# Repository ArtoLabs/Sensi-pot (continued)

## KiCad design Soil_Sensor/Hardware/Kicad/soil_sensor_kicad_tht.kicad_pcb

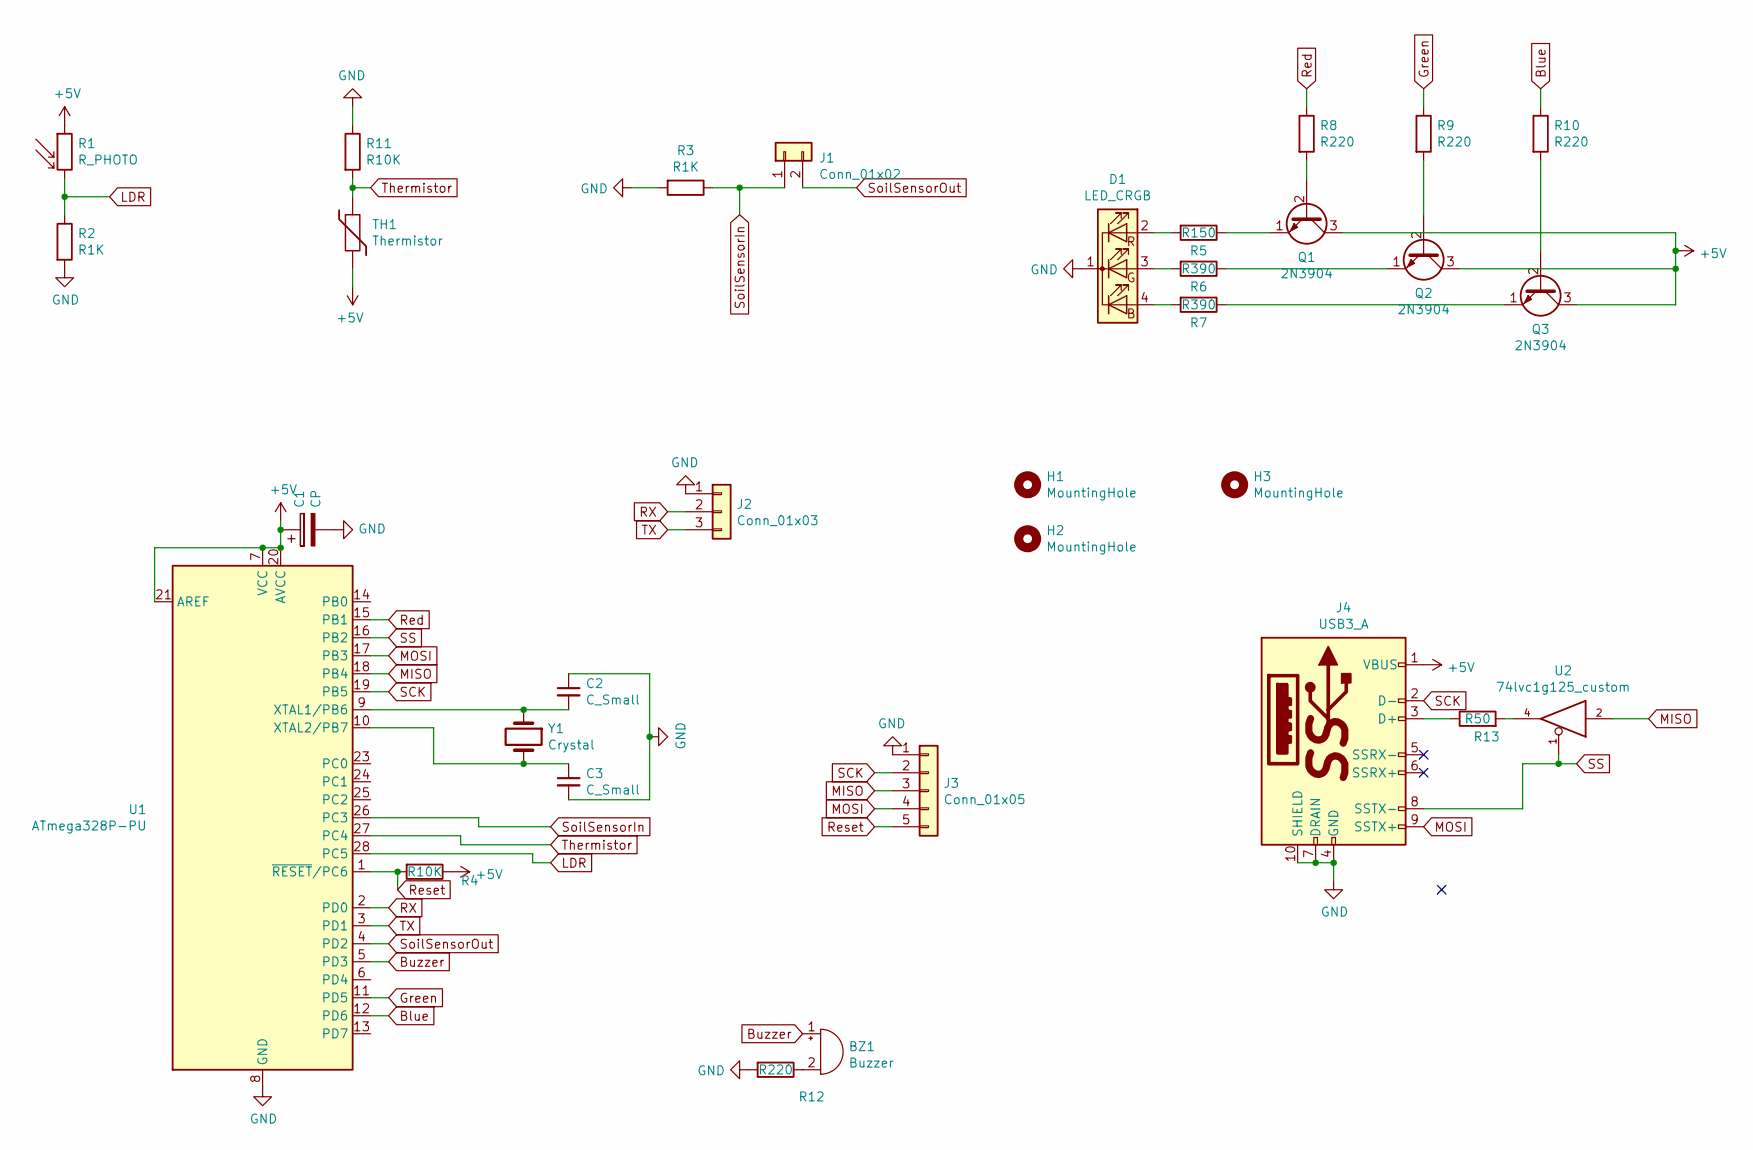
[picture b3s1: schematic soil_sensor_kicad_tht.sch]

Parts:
BZ1: Buzzer; Buzzer_12x9.5RM7.6
C1: CP; CP_Radial_D4.0mm_P1.50mm_bigger_pads
C2, C3: C_Small; C_Disc_D3.0mm_W1.6mm_P2.50mm
D1: LED_CRGB; LED_D5.0mm-4_RGB_Common_Cathode_2
H1, H2, H3: MountingHole; MountingHole_3.2mm_M3
J1: Conn_01x02; PinHeader_1x02_P2.54mm_Vertical
J2: Conn_01x03; PinHeader_1x03_P2.54mm_Vertical
J3: Conn_01x05; PinHeader_1x05_P2.54mm_Vertical
J4: USB3_A; USB3_A_Molex_Edited
Q1, Q2, Q3: 2N3904; TO-92_Inline_bigger_pads
R1: R_PHOTO; R_Axial_DIN0204_L3.6mm_D1.6mm_P1.90mm_Vertical
R2, R3: R1K; R_Axial_DIN0204_L3.6mm_D1.6mm_P7.62mm_Horizontal_bigger_pad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
R4, R11: R10K; R_Axial_DIN0204_L3.6mm_D1.6mm_P7.62mm_Horizontal_bigger_pad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
R5: R150; R_Axial_DIN0204_L3.6mm_D1.6mm_P7.62mm_Horizontal_bigger_pad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
R6, R7: R390; R_Axial_DIN0204_L3.6mm_D1.6mm_P7.62mm_Horizontal_bigger_pad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
R8, R9, R10, R12: R220; R_Axial_DIN0204_L3.6mm_D1.6mm_P7.62mm_Horizontal_bigger_pad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
R13: R50; R_Axial_DIN0204_L3.6mm_D1.6mm_P7.62mm_Horizontal_bigger_pad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
TH1: Thermistor; R_Axial_DIN0204_L3.6mm_D1.6mm_P1.90mm_Vertical
U1: ATmega328P-PU; DIP-28_W7.62mm
U2: 74lvc1g125_custom; SOT-23-5_HandSoldering
Y1: Crystal; Crystal_HC18-U_Vertical

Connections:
+5V: C1.1, J4.1 (VBUS), Q1.3 (C), Q2.3 (C), Q3.3 (C), R1.1, R4.1, TH1.2, U1.7 (VCC), U1.20 (AVCC), U1.21 (AREF), U2.5 (VCC)
Blue: R10.1, U1.12 (PD6)
Buzzer: BZ1.1 (-), U1.5 (PD3)
GND: C1.2, C2.1, C3.2, D1.1 (K), J2.1, J3.1, J4.4 (GND), J4.7 (DRAIN), J4.10 (SHIELD), R2.2, R3.2, R11.1, R12.2, U1.8 (GND), U1.22 (GND), U2.3 (GND)
Green: R9.1, U1.11 (PD5)
LDR: R1.2, R2.1, U1.28 (PC5)
MISO: J3.3, U1.18 (PB4), U2.2
MOSI: J3.4, J4.9 (SSTX+), U1.17 (PB3)
unnamed: BZ1.2 (+), R12.1
unnamed: C2.2, U1.9 (XTAL1/PB6), Y1.1
unnamed: C3.1, U1.10 (XTAL2/PB7), Y1.2
unnamed: D1.2 (RA), R5.2
unnamed: D1.3 (GA), R6.2
unnamed: D1.4 (BA), R7.2
unnamed: J4.3 (D+), R13.1
unnamed: Q1.1 (E), R5.1
unnamed: Q1.2 (B), R8.2
unnamed: Q2.1 (E), R6.1
unnamed: Q2.2 (B), R9.2
unnamed: Q3.1 (E), R7.1
unnamed: Q3.2 (B), R10.2
unnamed: R13.2, U2.4
RX: J2.2, U1.2 (PD0)
Red: R8.1, U1.15 (PB1)
Reset: J3.5, R4.2, U1.1 (~RESET~/PC6)
SCK: J3.2, J4.2 (D-), U1.19 (PB5)
SS: J4.8 (SSTX-), U1.16 (PB2), U2.1
SoilSensorIn: J1.1, R3.1, U1.26 (PC3)
SoilSensorOut: J1.2, U1.4 (PD2)
TX: J2.3, U1.3 (PD1)
Thermistor: R11.2, TH1.1, U1.27 (PC4)

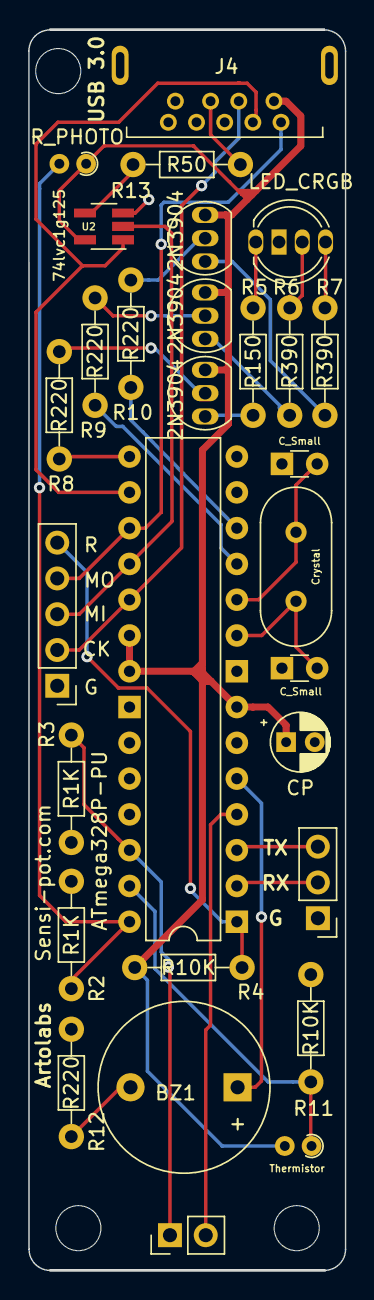
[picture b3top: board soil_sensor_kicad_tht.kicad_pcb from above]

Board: 2 copper layers, 22.5 x 88.1 mm, 32 parts (0 on the bottom side), 31 nets.

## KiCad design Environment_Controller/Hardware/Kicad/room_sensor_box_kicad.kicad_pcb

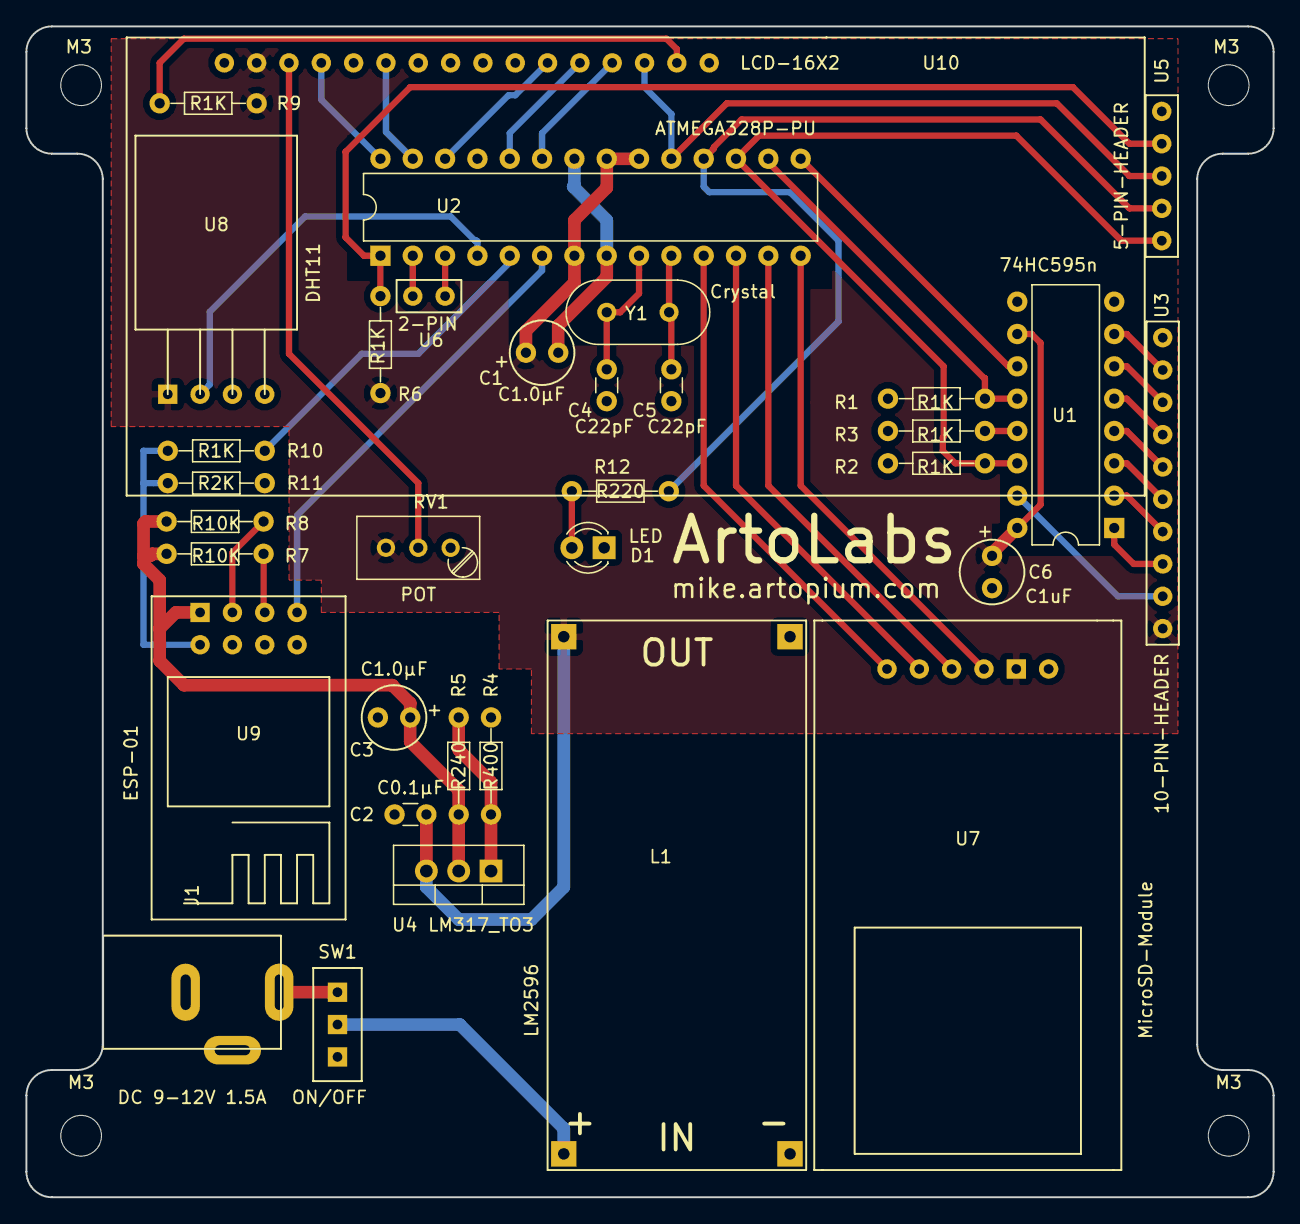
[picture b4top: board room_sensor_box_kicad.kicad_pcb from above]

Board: 2 copper layers, 98.0 x 92.0 mm, 34 parts (0 on the bottom side), 43 nets.

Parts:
C1, C3: C1.0µF; electrolytic_cap
C2: C0.1µF; disc_capacitor
C4, C5: C22pF; disc_capacitor
C6: C1uF; electrolytic_cap
D1: LED; LED_D3.0mm
J1: DC 9-12V 1.5A; DCJACK
L1: LM2596; lm2596-module_smaller_better_pads
R1, R2, R3, R6, R9, R10: R1K; 0.25_watt_resistor
R4: R400; 0.25_watt_resistor
R5: R240; 0.25_watt_resistor
R7, R8: R10K; 0.25_watt_resistor
R11: R2K; 0.25_watt_resistor
R12: R220; 0.25_watt_resistor
RV1: POT; Potentiometer_Trimmer_Bourns_3296W
SW1: ON/OFF; SWITCH
U1: 74HC595n; DIP-16_W7.62mm
U2: ATMEGA328P-PU; DIP-28_W7.62mm
U3: 10-PIN-HEADER; 10-PIN
U4: LM317_TO3; TO-220-3_Vertical
U5: 5-PIN-HEADER; 5-PIN
U6: 2-PIN
U7: MicroSD-Module; MICROSD
U8: DHT11
U9: ESP-01; ESP01
U10: LCD-16X2; LCD-16x2
Y1: Crystal; Crystal_HC18-U_Vertical

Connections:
+3V3: C3.1, R5.1, R7.2, R8.2, U4.3, U9.5
+5V: C1.1, C2.1, C6.1, L1.4, R6.1, R9.2, RV1.3, U1.10, U1.16, U2.7, U2.20, U2.21, U3.1, U4.2, U7.5, U8.4, U10.2
/DHT11: U2.4, U8.3
/DS_SER: R2.2, U1.14, U2.17, U5.1
/ESP-RXD: R10.1, U2.5
/ESP-TXD: U2.6, U9.8
/LCD-16X2-DB4: U2.26, U10.11
/LCD-16X2-DB5: U2.24, U10.12
/LCD-16X2-DB6: U2.23, U10.13
/LCD-16X2-DB7: U2.19, U5.3, U10.14
/LCD-16X2-E: U2.27, U10.6
/LCD-16X2-RS: U2.28, U10.4
/LED: R12.1, U2.18, U5.2
/MICROSD-CS: U2.11, U7.1
/MICROSD-MISO: U2.14, U7.4
/MICROSD-MOSI: U2.13, U7.3
/MICROSD-SCK: U2.12, U7.2
/SHCP_SRCLK: U1.11, U2.15
/STCP_RCLK: R1.2, U1.12, U2.16
GND: C1.2, C2.2, C3.2, C4.1, C5.1, C6.2, D1.1, J1.2, J1.3, L1.1, L1.3, R1.1, R2.1, R3.2, R4.2, R11.1, RV1.1, U1.8, U2.8, U2.22, U3.10, U5.5, U7.6, U8.1, U9.1, U10.1, U10.5, U10.16
unnamed: C4.2, U2.9, Y1.1
unnamed: C5.2, U2.10, Y1.2
unnamed: D1.2, R12.2
unnamed: J1.1, SW1.1
unnamed: L1.2, SW1.2
unnamed: R3.1, U1.13
unnamed: R4.1, R5.2, U4.1
unnamed: R6.2, U2.1, U5.4
unnamed: R7.1, U9.7
unnamed: R8.1, U9.6
unnamed: R9.1, U10.15
unnamed: R10.2, R11.2, U9.4
unnamed: RV1.2, U10.3
unnamed: U1.1, U3.3
unnamed: U1.2, U3.4
unnamed: U1.3, U3.5
unnamed: U1.4, U3.6
unnamed: U1.5, U3.7
unnamed: U1.6, U3.8
unnamed: U1.7, U3.9
unnamed: U1.15, U3.2
unnamed: U2.2, U6.1
unnamed: U2.3, U6.2

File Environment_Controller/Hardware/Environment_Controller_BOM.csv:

"Id";"Designator";"Package";"Quantity";"Designation";"Supplier and ref";
1;"D1";"LED_D3.0mm";1;"LED";;;
2;"SW1";"SWITCH";1;"SW_DIP_x01";;;
3;"U1";"DIP-16_W7.62mm";1;"74HC595n";;;
4;"U2";"DIP-28_W7.62mm";1;"ATMEGA328P-PU";;;
5;"U3";"10-PIN";1;"10-PIN-HEADER";;;
6;"U5";"5-PIN";1;"5-PIN-HEADER";;;
7;"U8";"DHT11";1;"DHT11";;;
8;"U9";"ESP01";1;"ESP-01";;;
9;"U10";"LCD-16x2";1;"LCD-16X2";;;
10;"Y1";"Crystal_HC18-U_Vertical";1;"Crystal";;;
11;"U4";"TO-220-3_Vertical";1;"LM317_TO3";;;
12;",,,";"MountingHole_3.2mm_M3";4;"M3";;;
13;"C1,C3";"electrolytic_cap";2;"C1.0µF";;;
14;"C2";"disc_capacitor";1;"C0.1µF";;;
15;"C4,C5";"disc_capacitor";2;"C22pF";;;
16;"R1,R2,R3,R6,R9,R10";"0.25_watt_resistor";6;"R1K";;;
17;"R4";"0.25_watt_resistor";1;"R390";;;
18;"R5";"0.25_watt_resistor";1;"R220";;;
19;"R7,R8";"0.25_watt_resistor";2;"R10K";;;
20;"R11";"0.25_watt_resistor";1;"R2K";;;
21;"R12";"0.25_watt_resistor";1;"R240";;;
22;"RV1";"Potentiometer_Trimmer_Bourns_3296W";1;"POT";;;
23;"J1";"DCJACK";1;"Jack-DC";;;
24;"L1";"lm2596-module_smaller_better_pads";1;"LM2596";;;
25;"C6";"electrolytic_cap";1;"C1uF";;;
26;"U6";"3-PIN";1;"3-PIN-HEADER";;;
27;"U7";"MICROSD2";1;"MicroSD-Module";;;

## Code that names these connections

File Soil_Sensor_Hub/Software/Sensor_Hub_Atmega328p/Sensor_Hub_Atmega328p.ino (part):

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}

short int devSSPins[8] = {8, 7, 6, 5, 15, 14, 10, 9}; // List of pins used to slave select for the 8 "USB" ports
// Pin 8 -> SS1A -> SS3 -> J4 -> MISO3 -> D3 -> H H L
// Pin 9 -> SS8A -> SS6 -> J9 -> MISO6 -> D7 -> H H H
// Pin 10 -> SS7A -> SS5 -> J8 -> MISO5 -> D6 -> L H H
// Pin 14 -> SS6A -> SS8 -> J11 -> MISO8 -> D5 -> H L H
// Pin 15 -> SS5A -> SS7 -> J10 -> MISO7 -> D4 -> L L H
// Pin 5 -> SS4A -> SS2 -> J3 -> MISO2 -> D0 -> L L L
// Pin 6 -> SS3A -> SS1 -> J1 -> MISO1 -> D1 -> H L L
// Pin 7 -> SS2A -> SS4 -> J6 -> MISO4 -> D2 -> L H L

uint32_t lastKnownAddr;
unsigned long loggingInterval = 300000;  // log every 5 minutes
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  }
  else if (receivedChars[0] == 'a') {
    short int d = receivedChars[1] - '0';
    if (sendCommand(devSSPins[d-1], 3)) { Serial.println(F("Alarm activated")); }
    else { Serial.println(F("Location alarm not activated: device did not respond")); }
  }
  newData = false;
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
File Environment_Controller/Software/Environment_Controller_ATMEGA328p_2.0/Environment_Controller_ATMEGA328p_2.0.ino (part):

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#define CS_PIN 5
#define CURRENT_UNIX_TIMESTAMP 1550447210 // This is only used for demonstration purposes and should be replaced (Approx Feb 17 16:50)

#define backlight 6

#define dataPin 8 // SER orange wire DS Data Pin 14 
#define latchPin 10 // SRCLK blue wire STCP Latch Pin 11 (Output Clock / Storage register clock pin)
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const byte relay5 = 0x08; //0b00001000    FAN 1
const byte relay6 = 0x04; //0b00000100    FAN 2
const byte relay7 = 0x02; //0b00000010    FAN 3
const byte relay8 = 0x01; //0b00000001    ALARM
const byte allOff = 0x00;
const byte allOn = 0xFF;

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

// User defined variables
const long alarmWaitPeriod = 240000; //600000; // wait 10 minutes before triggering alarm
const long slaveInterval = 15000;  // Check every 15 seconds
const long loggingInterval = 60000; //300000;  // log every 5 minutes
const int targetTemp = 75;
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void requestHumTemp() {  // The DHT11 is polled to find the temp and humidity

    int err = SimpleDHTErrSuccess;
    if ((err = dht11.read(pinDHT11, &temperature, &humidity, NULL)) != SimpleDHTErrSuccess) {
        // If the DHT11 encounters an error print it to the LCD
        lcd.clear();
        lcd.print(F("DHT11 error:    "));
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    pinMode(dataPin, OUTPUT);
    pinMode(latchPin, OUTPUT);
    pinMode(clockPin, OUTPUT);
    pinMode(backlight, OUTPUT);
    writeReg(allOn); // Turn all devices off: shift regisiter is inverting
    if (checkLDR()) { digitalWrite(backlight, LOW); }
    else { digitalWrite(backlight, HIGH); }
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
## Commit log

2019-02-07 Updated arduino code with comments and put the files into appropriate folders.
2019-02-08 Added BOM file
2019-02-08 Added schematic jpg
2019-02-08 Updated the readme file
2019-02-15 Uncommented critical lines of code. Sorry!
2019-02-15 Uncommented critical lines of code. Updated the logging timer to log only every 5 minutes although it still checks temp and humidity every 15 seconds and activates devices based on that.
2019-02-18 Removed comments
2019-02-19 Added software for soil sensor
    This software is based on i2c communication. The pcb for this setup was already ordered when I decided that the spi standard is a much better way to go. So this version will be updated very shortly a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
2019-04-12 Rough draft prototype schematics
2019-04-12 schematic added for soil sensor
2019-09-20 New software for new boards.
2020-01-15 Upgrade to 2.0
    Here we go Woo hoo!
